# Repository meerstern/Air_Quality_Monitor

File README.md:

# エアクオリティモニタ 
 Air Quality Monitor with ZMOD4410 & HS3001

  ※ 写真は使用イメージです リップスティック、USBケーブル等は含まれません  

 ## 概要 
  *  [室内空気質（IAQ）センサZMOD4410][1]及び[温湿度センサHS3001][2]を搭載したエアクオリティモニタです 
  * スティック状の小型な本体にCO2値、IAQ(屋内空気質基準)、温度、湿度を表示することができます  
  * 電源はmicroUSBを介してUSB電源(5V/300mA)で駆動します  
  * CO2計算アルゴリズムはメーカ提供の学習済みニューラルネットワークを使用したファームウェアを使用しています  
  * 学習済みニューラルネットワークによって従来よりもより正確にCO2値（eCO2）を推定できます  
  * LEDでIAQ(屋内空気質基準IAQ:2以下 青、2-3:青、黄、3-4:黄、4-5:黄、赤、5以上:赤)を確認できます 
  * 過去10時間の推移をグラフで簡易的に確認することができます  
  * 寝室等での利用を想定し、周辺の明るさに応じてLEDとディスプレイの輝度が低下します  
  * ボタン切り替えでCO2表示モード、温度表示モード、湿度表示モード、IAQ表示モードの切り替えが可能です  

  |  項目  |  範囲  | 
| ---- | ---- | 
|  温度  |  -40-125℃  |   
|  湿度  |  0-100%RH  | 
|  CO2  |  400-5000ppm  |  
|  IAQ  |  1.0-5.0  |  
    
 ドイツ環境庁（UBA）の屋内空気質（IAQ）基準
 
  |  IAQ  |  レベル  |  LED  |
| ---- | ---- | ---- |
|  <2  |  非常に良い  |  青  |
|  2~3  |  良い  |  青と黄  |
|  3~4  |  中間  |  黄  |
|  4~5  |  悪い  |  黄と赤  |
|  5~  |  非常に悪い | 赤 |

## 各部説明 
　

## サイズ
　幅7.5cm × 高さ2cm × 奥行 1.5cm (突起部除く)

## 注意 
 * 本センサはMOX(Metal Oxide)式のCO2センサのため、空気中の有機物から間接的にCO2に換算します  
 * 厳密なCO2計測には向きません  
 * 安定した測定をするために人通りや気流の変化が少ない場所に設置して使用してください  
 * キャリブレーション後にCO2値が安定するまで約0.5~1時間程度要します  
 * IAQは総合的な空気質の指標のため、CO2値が低くても他の有機物が多い場合に高くなります  
 * 電源投入後、2~3分はキャリブレーションのため、温湿度以外の値は未定で、全LEDが点灯します  
 * 約2秒周期で各センサの値を取得します(データ更新時にLEDが点滅します)  
 * センサのデータ応答が異常な場合、自動的に再起動する場合があります  
 * 再起動した場合はグラフの履歴がリセットされます  
 * 告知なしに仕様を変更する場合があります   
 * 背面のセンサ穴を塞がないように設置してください   

[1]: https://www.idt.com/jp/ja/products/sensor-products/gas-sensors/zmod4410-indoor-air-quality-sensor-platform
[2]: https://www.idt.com/us/ja/products/sensor-products/humidity-sensors/hs3001-high-performance-relative-humidity-and-temperature-sensor

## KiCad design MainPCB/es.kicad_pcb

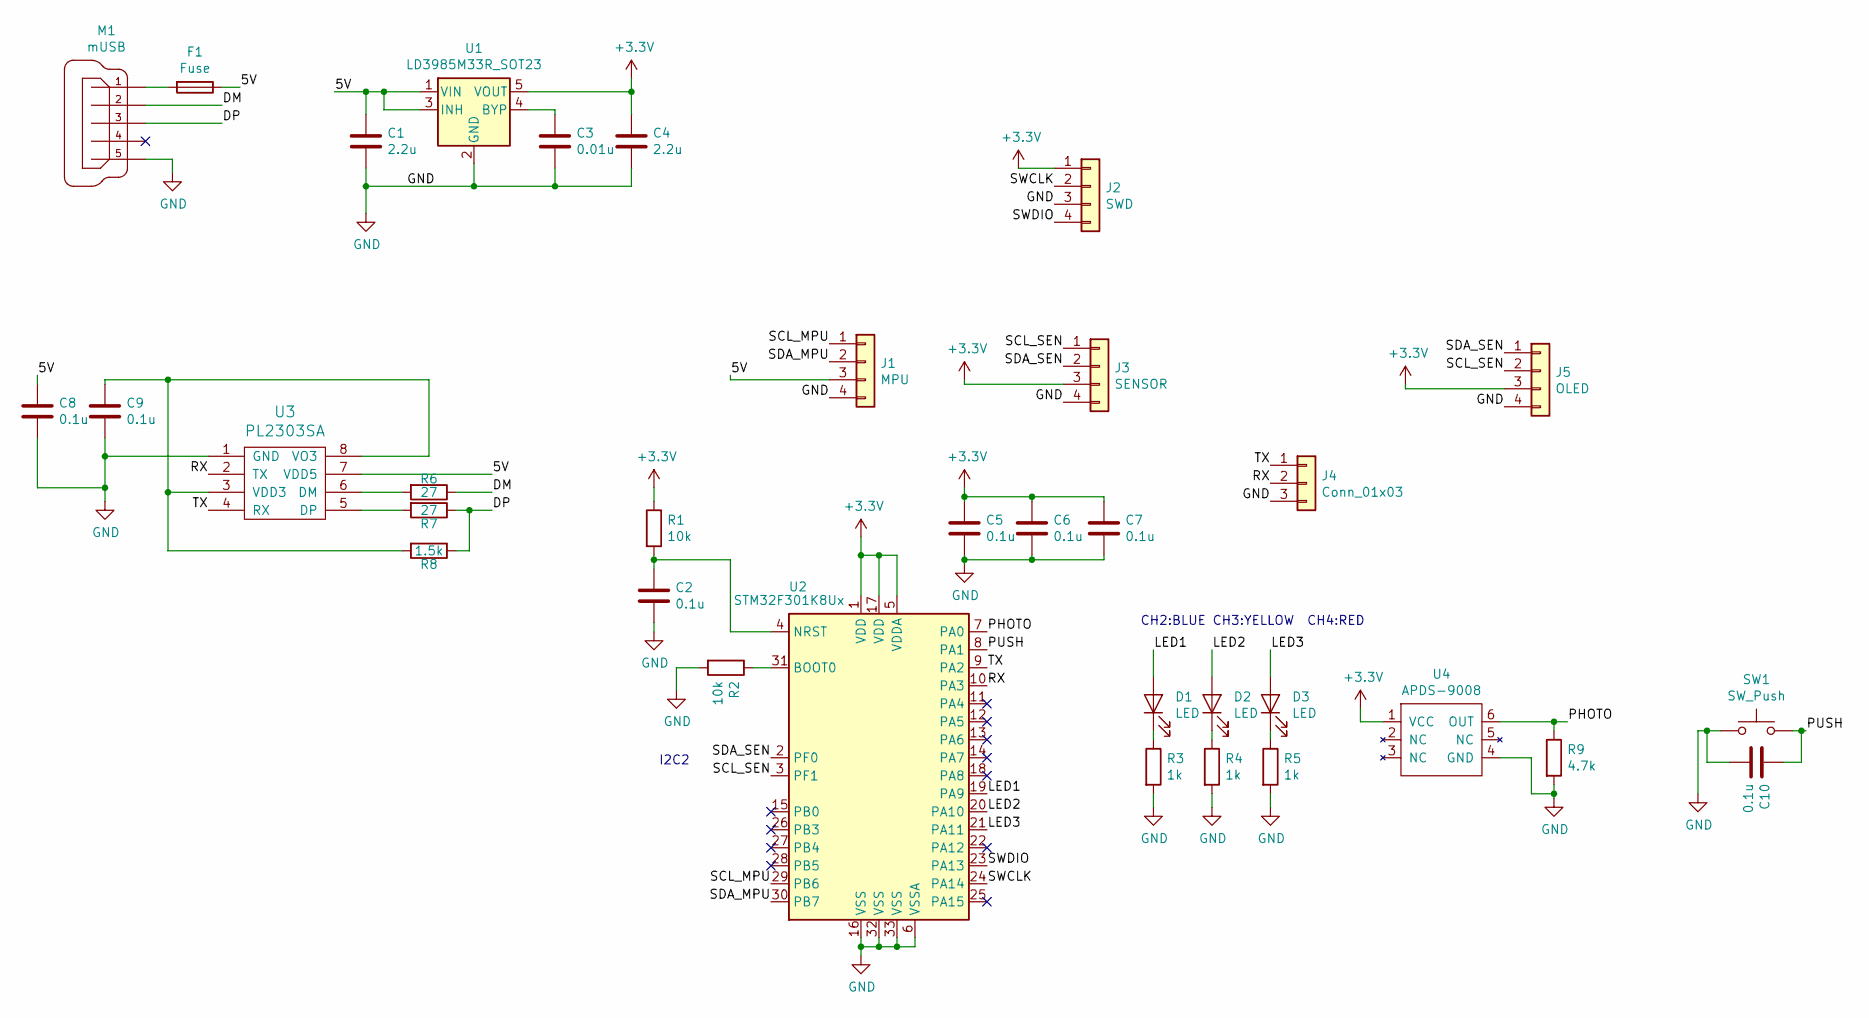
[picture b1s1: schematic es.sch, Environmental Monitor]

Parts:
C1, C4: 2.2u; C_0805_2012Metric
C2, C5, C6, C7, C8, C9, C10: 0.1u; C_0603_1608Metric
C3: 0.01u; C_0603_1608Metric
D1, D2, D3: LED; D_0603_1608Metric
F1: Fuse; Fuse_0603_1608Metric
J1: MPU; GROVE
J2: SWD; PinHeader_1x04_P2.54mm_Vertical
J3: SENSOR; GROVE
J4: Conn_01x03; PinHeader_1x03_P2.54mm_Vertical
J5: OLED; PinHeader_1x04_P2.54mm_Vertical
M1: mUSB; CONN-10118194-0001LF-FCI
R1, R2: 10k; R_0603_1608Metric
R3, R4, R5: 1k; R_0603_1608Metric
R6, R7: 27; R_0603_1608Metric
R8: 1.5k; R_0603_1608Metric
R9: 4.7k; R_0603_1608Metric
SW1: SW_Push; SKRPACE010
U1: LD3985M33R_SOT23; SOT-23-5
U2: STM32F301K8Ux; QFN-32-1EP_5x5mm_P0.5mm_EP3.45x3.45mm
U3: PL2303SA; SO-8_3.9x4.9mm_P1.27mm
U4: APDS-9008

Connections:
+3V3: C4.1, C5.1, C6.1, C7.1, J2.1, J3.3, J5.3, R1.1, U1.5 (VOUT), U2.1 (VDD), U2.5 (VDDA), U2.17 (VDD), U4.1 (VCC)
/5V: C1.1, C8.1, F1.1, J1.3, U1.1 (VIN), U1.3 (INH), U3.7 (VDD5)
/DM: M1.2, R6.1
/DP: M1.3, R7.1, R8.1
/LED1: D1.2 (A), U2.19 (PA9)
/LED2: D2.2 (A), U2.20 (PA10)
/LED3: D3.2 (A), U2.21 (PA11)
/PHOTO: R9.1, U2.7 (PA0), U4.6 (OUT)
/PUSH: C10.1, SW1.2, U2.8 (PA1)
/RX: J4.2, U2.10 (PA3), U3.2 (TX)
/SCL_MPU: J1.1, U2.29 (PB6)
/SCL_SEN: J3.1, J5.2, U2.3 (PF1)
/SDA_MPU: J1.2, U2.30 (PB7)
/SDA_SEN: J3.2, J5.1, U2.2 (PF0)
/SWCLK: J2.2, U2.24 (PA14)
/SWDIO: J2.4, U2.23 (PA13)
/TX: J4.1, U2.9 (PA2), U3.4 (RX)
GND: C1.2, C2.2, C3.2, C4.2, C5.2, C6.2, C7.2, C8.2, C9.2, C10.2, J1.4, J2.3, J3.4, J4.3, J5.4, M1.5, R2.2, R3.2, R4.2, R5.2, R9.2, SW1.1, U1.2 (GND), U2.6 (VSSA), U2.16 (VSS), U2.32 (VSS), U2.33 (VSS), U3.1 (GND), U4.4 (GND)
unnamed: C2.1, R1.2, U2.4 (NRST)
unnamed: C3.1, U1.4 (BYP)
unnamed: C9.1, R8.2, U3.3 (VDD3), U3.8 (VO3)
unnamed: D1.1 (K), R3.1
unnamed: D2.1 (K), R4.1
unnamed: D3.1 (K), R5.1
unnamed: F1.2, M1.1
unnamed: R2.1, U2.31 (BOOT0)
unnamed: R6.2, U3.6 (DM)
unnamed: R7.2, U3.5 (DP)

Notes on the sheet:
I2C2
CH2:BLUE
CH3:YELLOW
CH4:RED

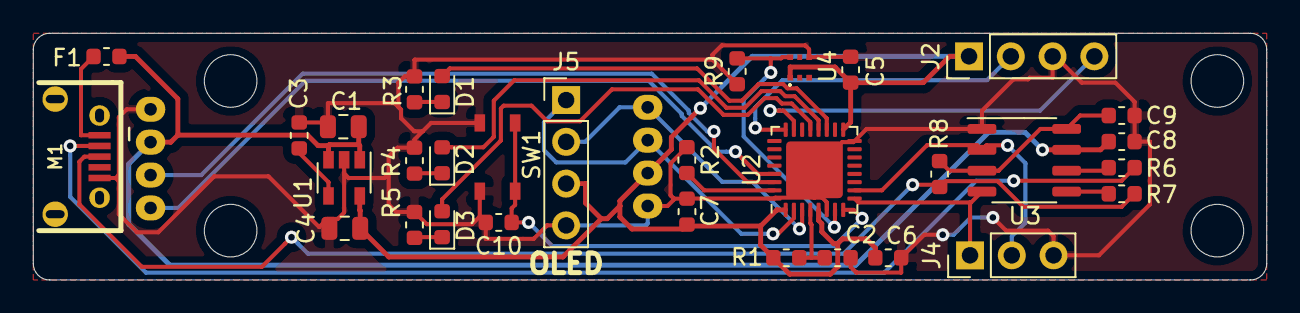
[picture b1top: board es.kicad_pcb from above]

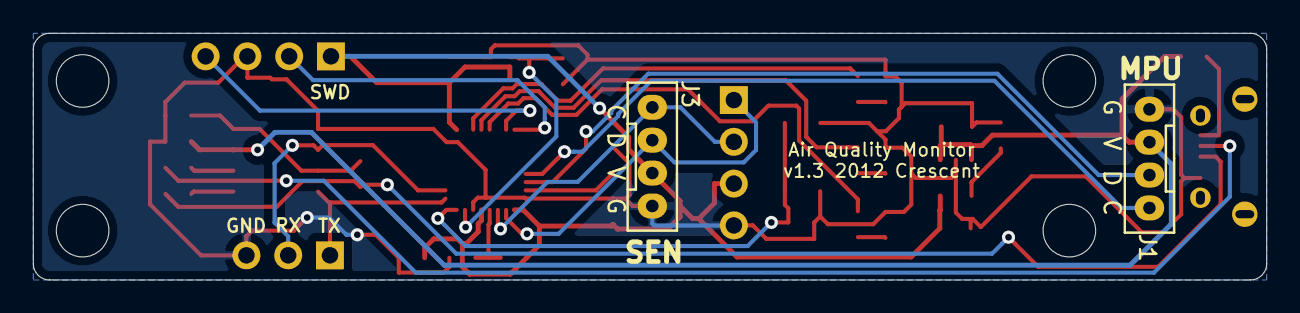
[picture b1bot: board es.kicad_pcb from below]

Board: 2 copper layers, 75.0 x 15.0 mm, 38 parts (2 on the bottom side), 28 nets.

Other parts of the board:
REF1, REF2, REF3, REF4: MountingHole_3.2mm_M3

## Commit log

2021-06-30 Add Main PCB Files
2021-06-30 Add Sensor PCB Files
2021-07-10 Add README
2022-03-27 Add images
2022-03-28 add image
